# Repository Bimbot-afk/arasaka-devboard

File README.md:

# Arasaka DevBoard

A custom development board hardware project designed in KiCad.
It has a cool design based on Arasaka from Cyberpunk 2077 >:D

## Hardware Specifications & BOM

The board is built around the RP2040 ecosystem using high-density SMD components (mostly 0402 imperial footprint).

*   **Microcontroller (MCU):** Raspberry Pi RP2040 (Dual ARM Cortex-M0+ @ 133MHz, QFN-56)
*   **Storage:** Winbond W25Q128JVSIQ (16MB SPI Flash, SOIC-8)
*   **Power Management:** onsemi NCP1117ST33T3G (3.3V LDO Linear Regulator, SOT-223)
*   **Clock / Timing:** YXC 12MHz Crystal Oscillator (SMD 3225-4P)
*   **Interfacing:** Korean Hroparts TYPE-C-31-M-12 (USB-C Receptacle, 16-pin SMD)
*   **Electromechanical:** ALPS SKRKAEE020 (Tactile Switch for BOOTSEL/RESET)
*   **Passives:** Standard 0402 and 0603 ceramic capacitors (X5R/X7R dielectrics) and thick film resistors (1% tolerance on USB data lines).
*   **Expansion:** 2.54mm pitch through-hole pin headers.

## Schematics

## Layers

### F.cu

### B.cu

### Both

### Front

### BACK

## Project Structure

- **`3D_Models/`**: Contains 3D assets (`.step`, `.glb`, `.blend`) for the board and components.
- **`Fabrication/`**: Destination folder for generated manufacturing files like Gerbers, drill files, and BOMs.
- **`Libraries/`**: Project-specific footprints and symbols (e.g., custom Arasaka assets).
- **Core Files**: The main KiCad project files (`.kicad_pro`, `.kicad_sch`, `.kicad_pcb`) are located in the root directory.

## Getting Started

To view or modify this project, you will need [KiCad](https://www.kicad.org/) (Version 6+ recommended). 

1. Clone this repository.
2. Open the `devBoard.kicad_pro` file in KiCad to load the project.

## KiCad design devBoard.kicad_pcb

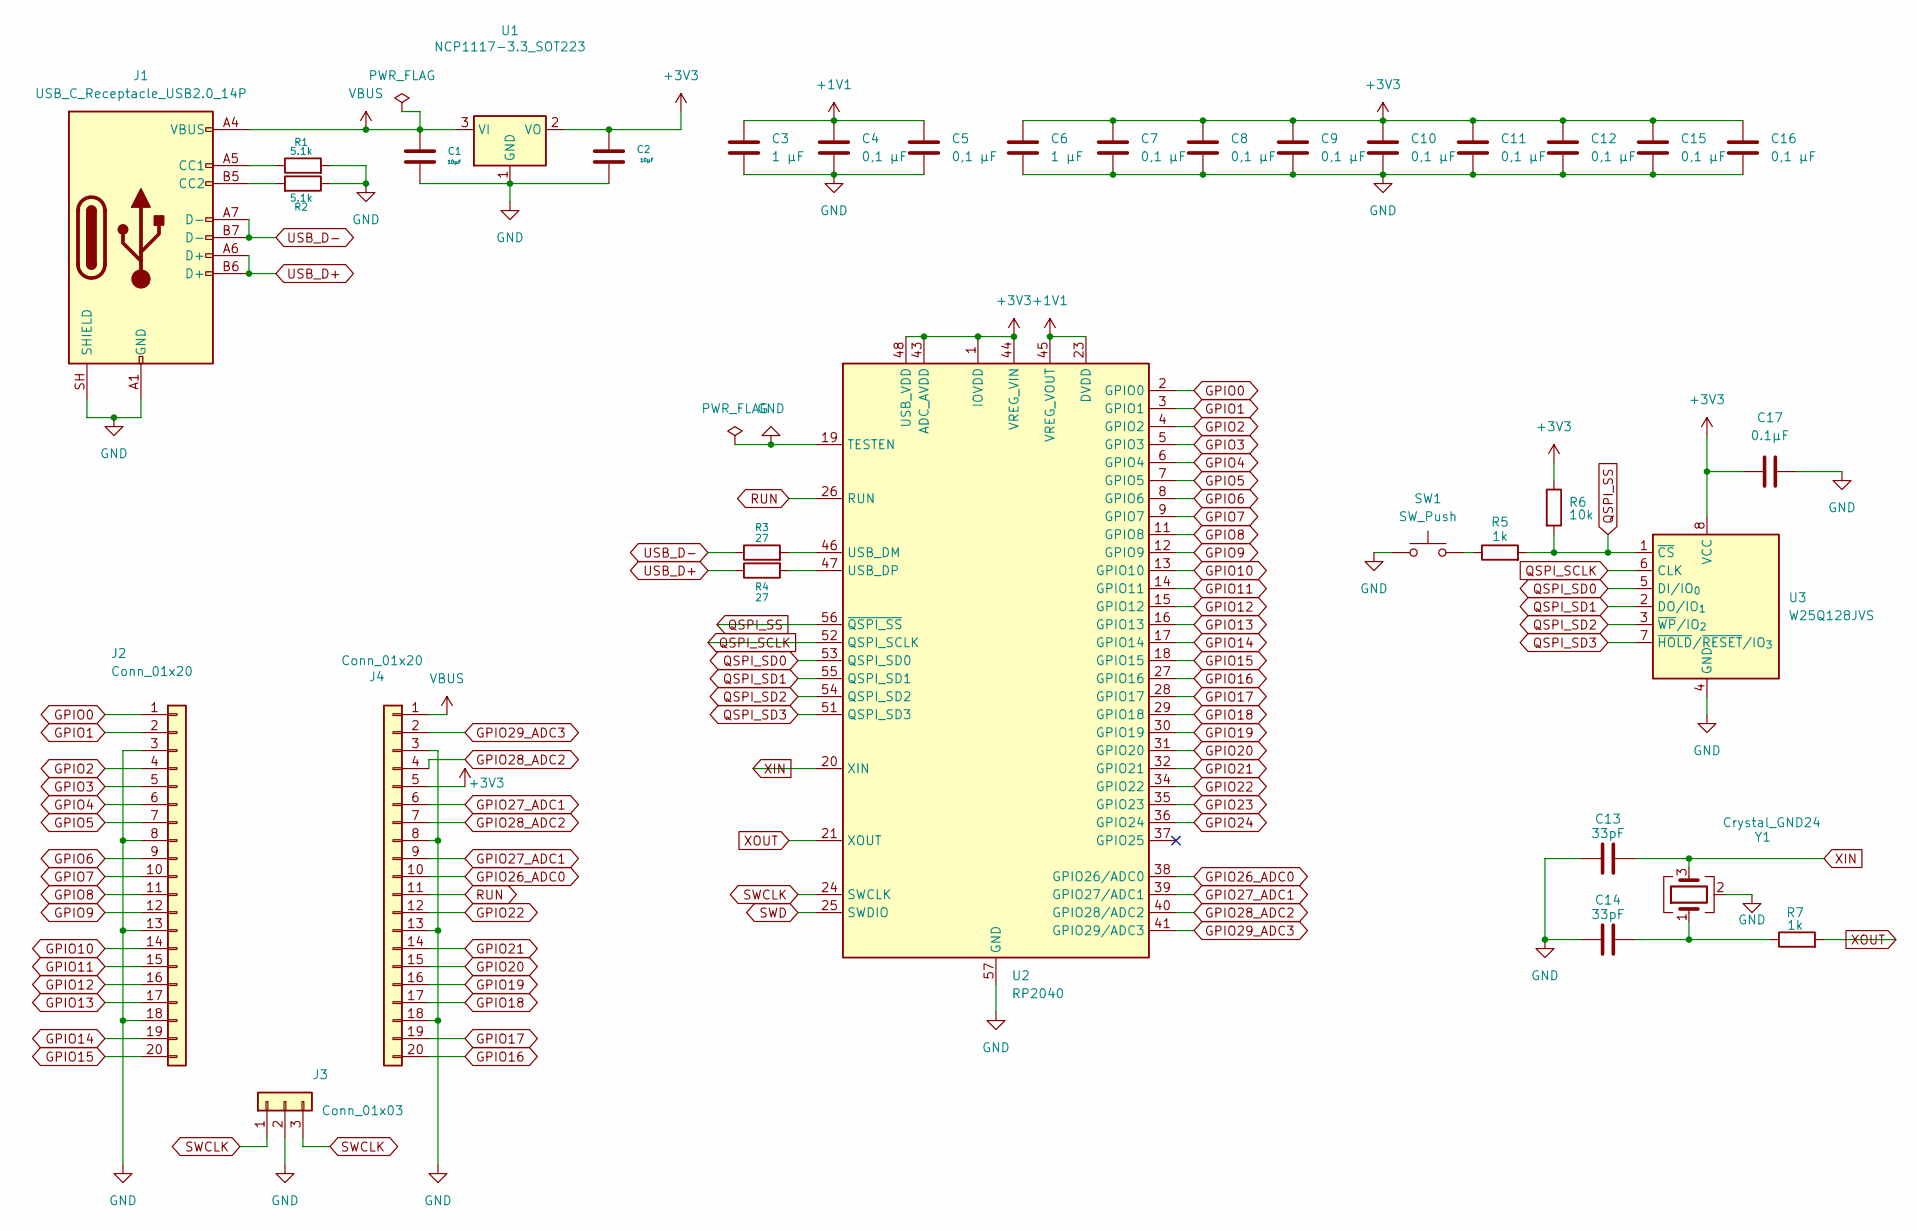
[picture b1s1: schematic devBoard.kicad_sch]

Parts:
C1, C2: 10μF; C_0603_1608Metric
C3, C6: 1 μF; C_0402_1005Metric
C4, C5, C7, C8, C9, C10, C11, C12, C15, C16: 0,1 μF; C_0402_1005Metric
C13, C14: 33pF; C_0402_1005Metric
C17: 0.1µF; C_0402_1005Metric
J1: USB_C_Receptacle_USB2.0_14P; USB_C_Receptacle_HRO_TYPE-C-31-M-12
J2, J4: Conn_01x20; PinHeader_1x20_P2.54mm_Vertical
J3: Conn_01x03; PinHeader_1x03_P2.54mm_Vertical
R1, R2: 5.1k; R_0402_1005Metric
R3, R4: 27; R_0402_1005Metric
R5, R7: 1k; R_0402_1005Metric
R6: 10k; R_0402_1005Metric
SW1: SW_Push; SW_Push_SPST_NO_Alps_SKRK
U1: NCP1117-3.3_SOT223; SOT-223-3_TabPin2
U2: RP2040; QFN-56-1EP_7x7mm_P0.4mm_EP3.2x3.2mm
U3: W25Q128JVS; SOIC-8_5.3x5.3mm_P1.27mm
Y1: Crystal_GND24; Crystal_SMD_3225-4Pin_3.2x2.5mm

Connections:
+1V1: C3.1, C4.1, C5.1, U2.23 (DVDD), U2.45 (VREG_VOUT), U2.50 (DVDD)
+3V3: C2.1, C6.1, C7.1, C8.1, C9.1, C10.1, C11.1, C12.1, C15.1, C16.1, C17.1, J4.5, R6.1, U1.2 (VO), U2.1 (IOVDD), U2.10 (IOVDD), U2.22 (IOVDD), U2.33 (IOVDD), U2.42 (IOVDD), U2.43 (ADC_AVDD), U2.44 (VREG_VIN), U2.48 (USB_VDD), U2.49 (IOVDD), U3.8 (VCC)
GND: C1.2, C2.2, C3.2, C4.2, C5.2, C6.2, C7.2, C8.2, C9.2, C10.2, C11.2, C12.2, C13.1, C14.1, C15.2, C16.2, C17.2, J1.A1 (GND), J1.A12 (GND), J1.B1 (GND), J1.B12 (GND), J1.SH (SHIELD), J2.3, J2.8, J2.13, J2.18, J3.2, J4.3, J4.8, J4.13, J4.18, R1.2, R2.1, SW1.1, U1.1 (GND), U2.19 (TESTEN), U2.57 (GND), U3.4 (GND), Y1.2 (G), Y1.4 (G)
GPIO0: J2.1, U2.2 (GPIO0)
GPIO1: J2.2, U2.3 (GPIO1)
GPIO2: J2.4, U2.4 (GPIO2)
GPIO3: J2.5, U2.5 (GPIO3)
GPIO4: J2.6, U2.6 (GPIO4)
GPIO5: J2.7, U2.7 (GPIO5)
GPIO6: J2.9, U2.8 (GPIO6)
GPIO7: J2.10, U2.9 (GPIO7)
GPIO8: J2.11, U2.11 (GPIO8)
GPIO9: J2.12, U2.12 (GPIO9)
GPIO10: J2.14, U2.13 (GPIO10)
GPIO11: J2.15, U2.14 (GPIO11)
GPIO12: J2.16, U2.15 (GPIO12)
GPIO13: J2.17, U2.16 (GPIO13)
GPIO14: J2.19, U2.17 (GPIO14)
GPIO15: J2.20, U2.18 (GPIO15)
GPIO16: J4.20, U2.27 (GPIO16)
GPIO17: J4.19, U2.28 (GPIO17)
GPIO18: J4.17, U2.29 (GPIO18)
GPIO19: J4.16, U2.30 (GPIO19)
GPIO20: J4.15, U2.31 (GPIO20)
GPIO21: J4.14, U2.32 (GPIO21)
GPIO22: J4.12, U2.34 (GPIO22)
GPIO23: U2.35 (GPIO23)
GPIO24: U2.36 (GPIO24)
GPIO26_ADC0: J4.10, U2.38 (GPIO26/ADC0)
GPIO27_ADC1: J4.6, J4.9, U2.39 (GPIO27/ADC1)
GPIO28_ADC2: J4.4, J4.7, U2.40 (GPIO28/ADC2)
GPIO29_ADC3: J4.2, U2.41 (GPIO29/ADC3)
unnamed: C14.2, R7.1, Y1.1
unnamed: J1.A5 (CC1), R1.1
unnamed: J1.B5 (CC2), R2.2
unnamed: R5.1, SW1.2
unnamed: R3.2, U2.46 (USB_DM)
unnamed: R4.2, U2.47 (USB_DP)
QSPI_SCLK: U2.52 (QSPI_SCLK), U3.6 (CLK)
QSPI_SD0: U2.53 (QSPI_SD0), U3.5 (DI/IO_{0})
QSPI_SD1: U2.55 (QSPI_SD1), U3.2 (DO/IO_{1})
QSPI_SD2: U2.54 (QSPI_SD2), U3.3 (~WP/IO_{2})
QSPI_SD3: U2.51 (QSPI_SD3), U3.7 (~HOLD/~RESET/IO_{3})
QSPI_SS: R5.2, R6.2, U2.56 (~QSPI_SS), U3.1 (~CS)
RUN: J4.11, U2.26 (RUN)
SWCLK: J3.1, J3.3, U2.24 (SWCLK)
SWD: U2.25 (SWDIO)
USB_D+: J1.A6 (D+), J1.B6 (D+), R4.1
USB_D-: J1.A7 (D-), J1.B7 (D-), R3.1
VBUS: C1.1, J1.A4 (VBUS), J1.A9 (VBUS), J1.B4 (VBUS), J1.B9 (VBUS), J4.1, U1.3 (VI)
XIN: C13.2, U2.20 (XIN), Y1.3
XOUT: R7.2, U2.21 (XOUT)

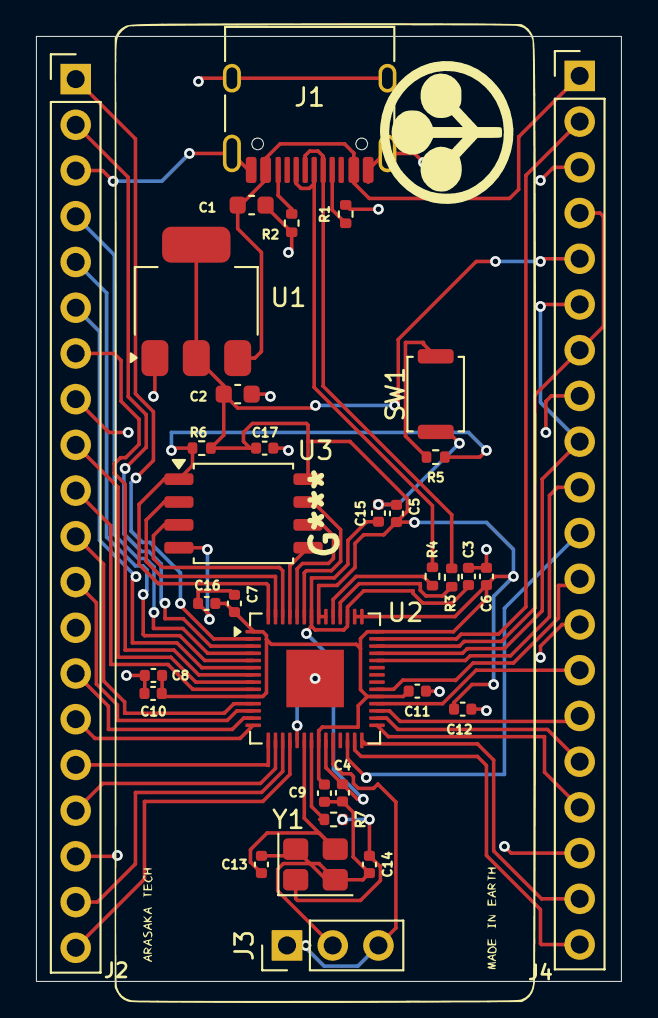
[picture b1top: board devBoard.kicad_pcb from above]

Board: 2 copper layers, 32.5 x 52.5 mm, 33 parts (0 on the bottom side), 49 nets.
